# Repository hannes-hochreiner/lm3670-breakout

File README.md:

# lm3670-breakout
Breakout board for the LM3670 DC-DC converter.

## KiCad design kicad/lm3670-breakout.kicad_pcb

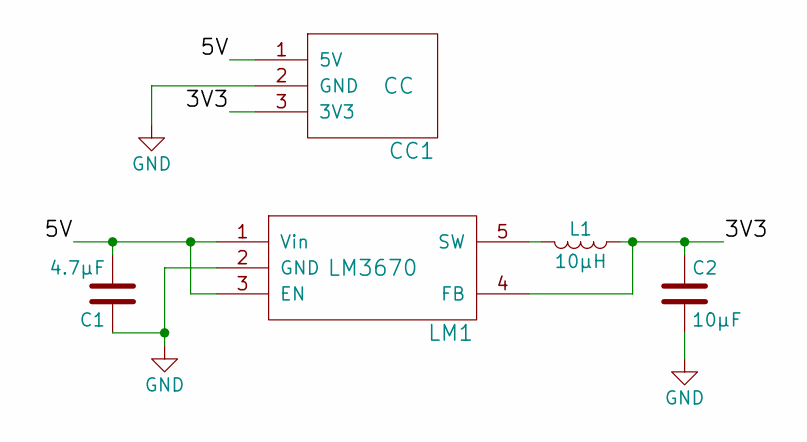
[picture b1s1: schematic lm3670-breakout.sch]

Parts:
C1: 4.7µF; R_0603_HandSoldering
C2: 10µF; R_0603_HandSoldering
CC1: CC; Pin_Header_Straight_1x03_Pitch2.54mm
L1: 10µH; INDUCTOR
LM1: LM3670; TSOT-23-5_HandSoldering

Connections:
/3V3: C2.1, CC1.3 (3V3), L1.1, LM1.4 (FB)
/5V: C1.2, CC1.1 (5V), LM1.1 (Vin), LM1.3 (EN)
GND: C1.1, C2.2, CC1.2 (GND), LM1.2 (GND)
unnamed: L1.2, LM1.5 (SW)

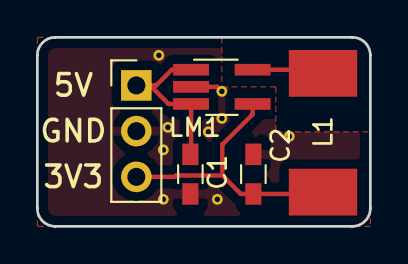
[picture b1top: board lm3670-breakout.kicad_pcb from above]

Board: 2 copper layers, 18.5 x 10.5 mm, 5 parts (0 on the bottom side), 4 nets.

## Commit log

2017-09-20 first version
2017-09-21 updated pcb
